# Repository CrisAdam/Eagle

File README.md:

# Eagle
A place for storing Eagle PCB designs and libraries

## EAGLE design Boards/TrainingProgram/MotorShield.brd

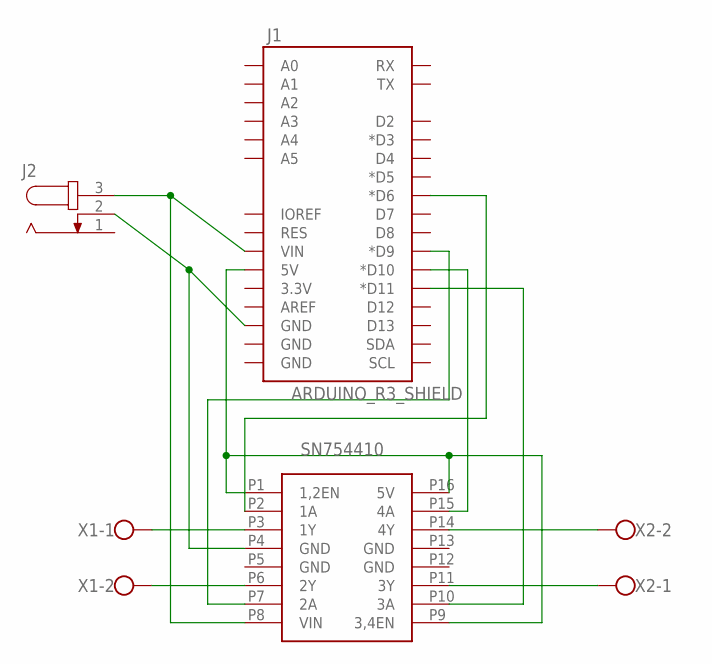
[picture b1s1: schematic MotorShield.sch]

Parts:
J1: ARDUINO_R3_SHIELD; UNO_R3_SHIELD
J2: JACK-PLUG1; SPC4078
U$1: TI_SN754410NEDIP16; DIP16
X1, X2: W237-102

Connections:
GND: U$1.P5 (GND), U$1.P12 (GND), U$1.P13 (GND)
unnamed: J1.VIN, J2.3, U$1.P8 (VIN)
unnamed: J1.GND@2 (GND), J2.2, U$1.P4 (GND)
unnamed: U$1.P14 (4Y), X2.2
unnamed: U$1.P11 (3Y), X2.1
unnamed: U$1.P6 (2Y), X1.2
unnamed: U$1.P3 (1Y), X1.1
unnamed: J1.5V, U$1.P1 (1,2EN), U$1.P9 (3,4EN), U$1.P16 (5V)
unnamed: J1.D11 (*D11), U$1.P10 (3A)
unnamed: J1.D10 (*D10), U$1.P15 (4A)
unnamed: J1.D9 (*D9), U$1.P7 (2A)
unnamed: J1.D6 (*D6), U$1.P2 (1A)

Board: 2 copper layers, 5 parts (0 on the bottom side), 12 nets, no tracks yet.

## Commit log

2016-02-26 initial
2016-03-03 added libraries
2016-03-03 added adafruit library
2016-03-05 connected holes to ground
2016-03-06 added motor driver library + sample circuit
2016-03-06 created sub-board for 6x9'' test
2016-03-06 added DRU
2016-03-20 updated ISC parts library
2016-03-25 removed part sizes from library
2016-03-26 removed drill holes from uno in isc library

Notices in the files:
parts and their libraries:
SparkFun-Boards: Licensing: Creative Commons ShareAlike 4.0 International - https://creativecommons.org/licenses/by-sa/4.0
